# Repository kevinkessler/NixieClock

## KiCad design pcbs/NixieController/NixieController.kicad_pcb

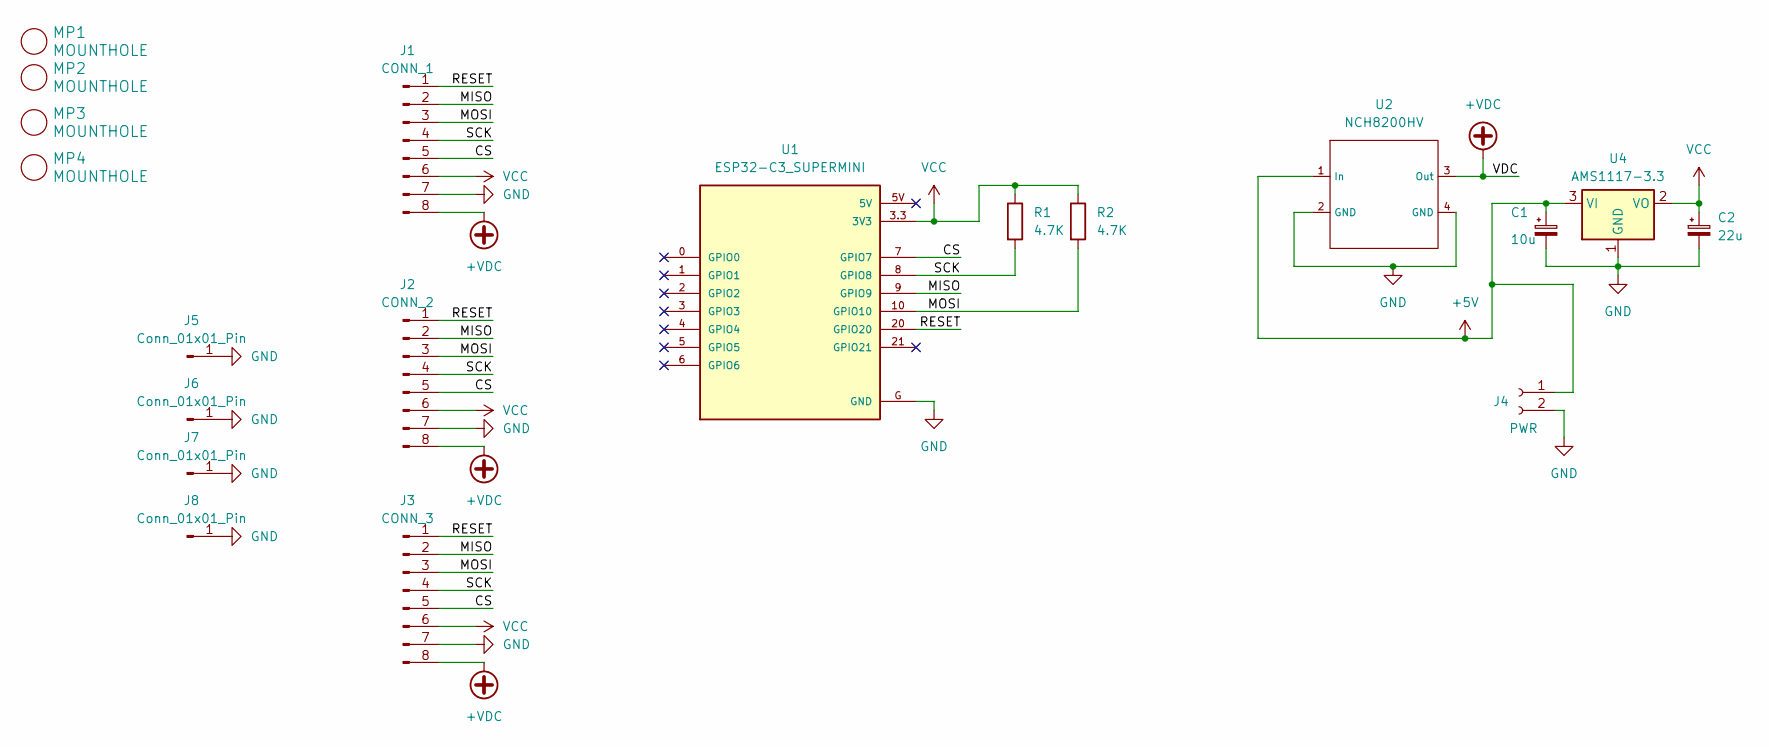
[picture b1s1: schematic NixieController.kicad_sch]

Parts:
C1: 10u; CP_Elec_5x5.3
C2: 22u; CP_Elec_6.3x7.7
J1: CONN_1; JST_PH_B8B-PH-K_1x08_P2.00mm_Vertical
J2: CONN_2; JST_PH_B8B-PH-K_1x08_P2.00mm_Vertical
J3: CONN_3; JST_PH_B8B-PH-K_1x08_P2.00mm_Vertical
J4: PWR; PinSocket_1x02_P2.54mm_Vertical
J5, J6, J7, J8: Conn_01x01_Pin; PinSocket_1x01_P2.54mm_Vertical
MP1, MP2, MP3, MP4: MOUNTHOLE; TH-M3
R1, R2: 4.7K; R_0805_2012Metric_Pad1.20x1.40mm_HandSolder
U1: ESP32-C3_SUPERMINI; MODULE_ESP32-C3_SUPERMINI
U2: NCH8200HV
U4: AMS1117-3.3; SOT-223-3_TabPin2

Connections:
+5V: C1.1, J4.1, U2.1 (In), U4.3 (VI)
+VDC: J1.8, J2.8, J3.8, U2.3 (Out)
/CS: J1.5, J2.5, J3.5, U1.7 (GPIO7)
/MISO: J1.2, J2.2, J3.2, U1.9 (GPIO9)
/MOSI: J1.3, J2.3, J3.3, R2.2, U1.10 (GPIO10)
/RESET: J1.1, J2.1, J3.1, U1.20 (GPIO20)
/SCK: J1.4, J2.4, J3.4, R1.2, U1.8 (GPIO8)
GND: C1.2, C2.2, J1.7, J2.7, J3.7, J4.2, J5.1, J6.1, J7.1, J8.1, U1.G (GND), U2.2 (GND), U2.4 (GND), U4.1 (GND)
VCC: C2.1, J1.6, J2.6, J3.6, R1.1, R2.1, U1.3.3 (3V3), U4.2 (VO)

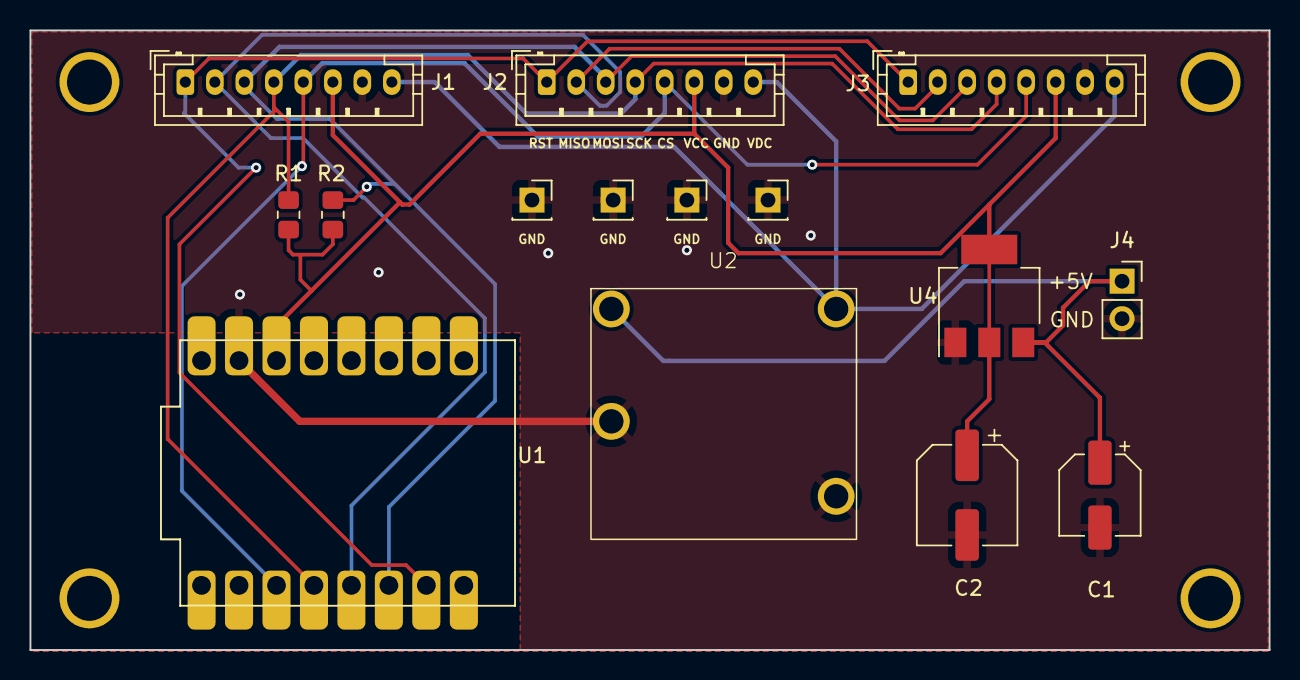
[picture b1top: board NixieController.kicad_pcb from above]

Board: 2 copper layers, 84.0 x 42.0 mm, 19 parts (0 on the bottom side), 9 nets.

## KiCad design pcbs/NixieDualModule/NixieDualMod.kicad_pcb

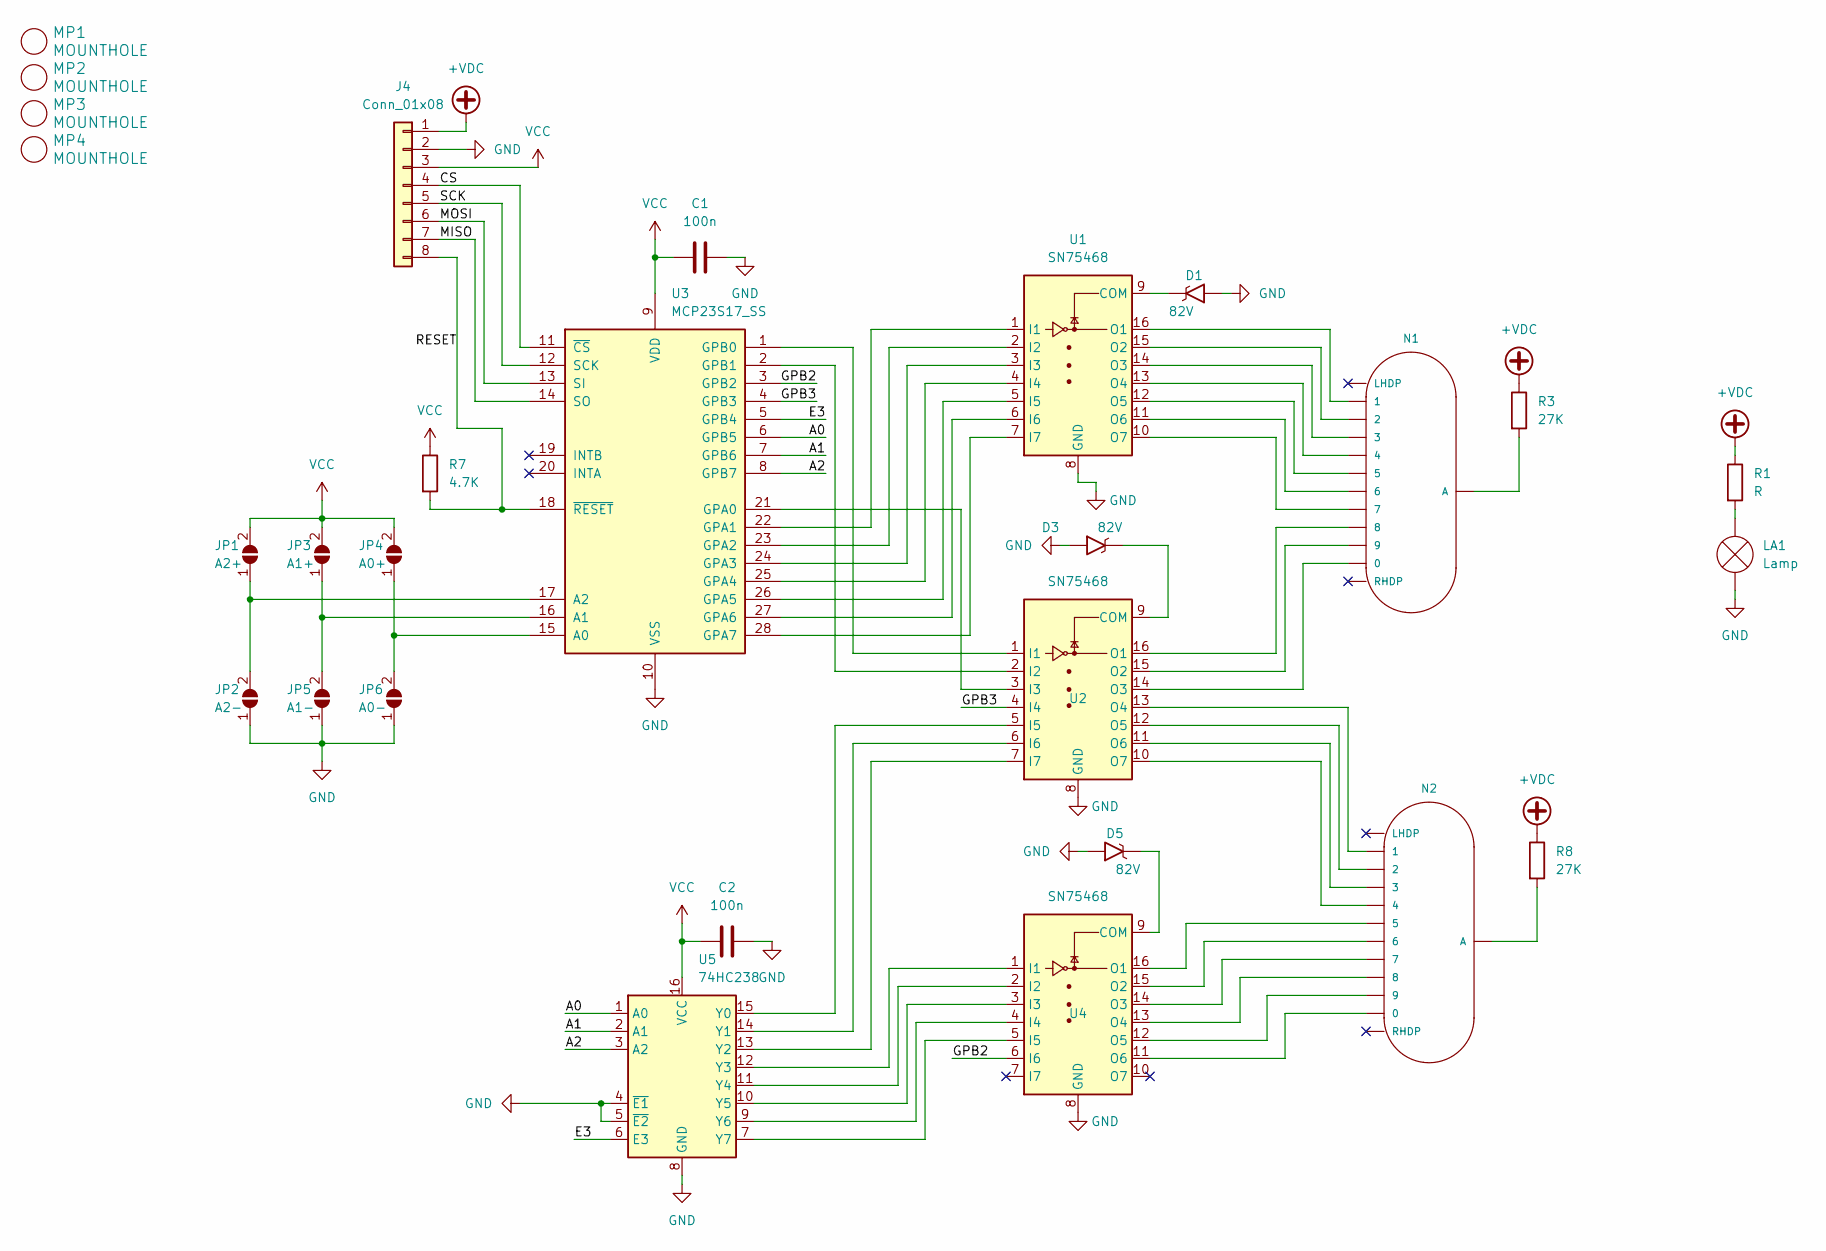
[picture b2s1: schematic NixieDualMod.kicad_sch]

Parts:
C1, C2: 100n; C_0805_2012Metric_Pad1.18x1.45mm_HandSolder
D1, D3, D5: 82V; Zener_SOT-23-3
J4: Conn_01x08; JST_PH_B8B-PH-K_1x08_P2.00mm_Vertical
JP1: A2+; SolderJumper-2_P1.3mm_Open_TrianglePad1.0x1.5mm
JP2: A2-; SolderJumper-2_P1.3mm_Open_TrianglePad1.0x1.5mm
JP3: A1+; SolderJumper-2_P1.3mm_Open_TrianglePad1.0x1.5mm
JP4: A0+; SolderJumper-2_P1.3mm_Open_TrianglePad1.0x1.5mm
JP5: A1-; SolderJumper-2_P1.3mm_Open_TrianglePad1.0x1.5mm
JP6: A0-; SolderJumper-2_P1.3mm_Open_TrianglePad1.0x1.5mm
LA1: Lamp; Valve_Glimm
MP1, MP2, MP3, MP4: MOUNTHOLE; TH-M3
N1, N2: IN-1; nixies-us-IN-14
R1: R; R_0805_2012Metric_Pad1.20x1.40mm_HandSolder
R3, R8: 27K; R_0805_2012Metric_Pad1.20x1.40mm_HandSolder
R7: 4.7K; R_0805_2012Metric_Pad1.20x1.40mm_HandSolder
U1, U2, U4: SN75468; SOIC-16_3.9x9.9mm_P1.27mm
U3: MCP23S17_SS; SOIC-28W_7.5x17.9mm_P1.27mm
U5: 74HC238; SOP-16_3.9x9.9mm_P1.27mm

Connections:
+VDC: J4.1, R1.1, R3.1, R8.1
/A0: U3.6 (GPB5), U5.1 (A0)
/A1: U3.7 (GPB6), U5.2 (A1)
/A2: U3.8 (GPB7), U5.3 (A2)
/CS: J4.4, U3.11 (~CS)
/E3: U3.5 (GPB4), U5.6 (E3)
/GPB2: U3.3 (GPB2), U4.6 (I6)
/GPB3: U2.4 (I4), U3.4 (GPB3)
/MISO: J4.7, U3.14 (SO)
/MOSI: J4.6, U3.13 (SI)
/RESET: J4.8, R7.2, U3.18 (~RESET)
/SCK: J4.5, U3.12 (SCK)
GND: C1.2, C2.2, D1.1 (A), D3.1 (A), D5.1 (A), J4.2, JP2.1 (A), JP5.1 (A), JP6.1 (A), LA1.1 (-), U1.8 (GND), U2.8 (GND), U3.10 (VSS), U4.8 (GND), U5.4 (~E1), U5.5 (~E2), U5.8 (GND)
unnamed: D1.3 (K), U1.9 (COM)
unnamed: D3.3 (K), U2.9 (COM)
unnamed: D5.3 (K), U4.9 (COM)
unnamed: JP1.1 (A), JP2.2 (B), U3.17 (A2)
unnamed: JP3.1 (A), JP5.2 (B), U3.16 (A1)
unnamed: JP4.1 (A), JP6.2 (B), U3.15 (A0)
unnamed: LA1.2 (+), R1.2
unnamed: N1.A, R3.2
unnamed: N2.A, R8.2
unnamed: U1.1 (I1), U3.22 (GPA1)
unnamed: U1.2 (I2), U3.23 (GPA2)
unnamed: U1.3 (I3), U3.24 (GPA3)
unnamed: U1.4 (I4), U3.25 (GPA4)
unnamed: U1.5 (I5), U3.26 (GPA5)
unnamed: U1.6 (I6), U3.27 (GPA6)
unnamed: U1.7 (I7), U3.28 (GPA7)
unnamed: N1.1, U1.16 (O1)
unnamed: N1.2, U1.15 (O2)
unnamed: N1.3, U1.14 (O3)
unnamed: N1.4, U1.13 (O4)
unnamed: N1.5, U1.12 (O5)
unnamed: N1.6, U1.11 (O6)
unnamed: N1.7, U1.10 (O7)
unnamed: U2.1 (I1), U3.1 (GPB0)
unnamed: U2.2 (I2), U3.2 (GPB1)
unnamed: U2.3 (I3), U3.21 (GPA0)
unnamed: U2.5 (I5), U5.15 (Y0)
unnamed: U2.6 (I6), U5.14 (Y1)
unnamed: U2.7 (I7), U5.13 (Y2)
unnamed: N1.8, U2.16 (O1)
unnamed: N1.9, U2.15 (O2)
unnamed: N1.0, U2.14 (O3)
unnamed: N2.1, U2.13 (O4)
unnamed: N2.2, U2.12 (O5)
unnamed: N2.3, U2.11 (O6)
unnamed: N2.4, U2.10 (O7)
unnamed: U4.1 (I1), U5.12 (Y3)
unnamed: U4.2 (I2), U5.11 (Y4)
unnamed: U4.3 (I3), U5.10 (Y5)
unnamed: U4.4 (I4), U5.9 (Y6)
unnamed: U4.5 (I5), U5.7 (Y7)
unnamed: N2.5, U4.16 (O1)
unnamed: N2.6, U4.15 (O2)
unnamed: N2.7, U4.14 (O3)
unnamed: N2.8, U4.13 (O4)
unnamed: N2.9, U4.12 (O5)
unnamed: N2.0, U4.11 (O6)
VCC: C1.1, C2.1, J4.3, JP1.2 (B), JP3.2 (B), JP4.2 (B), R7.1, U3.9 (VDD), U5.16 (VCC)

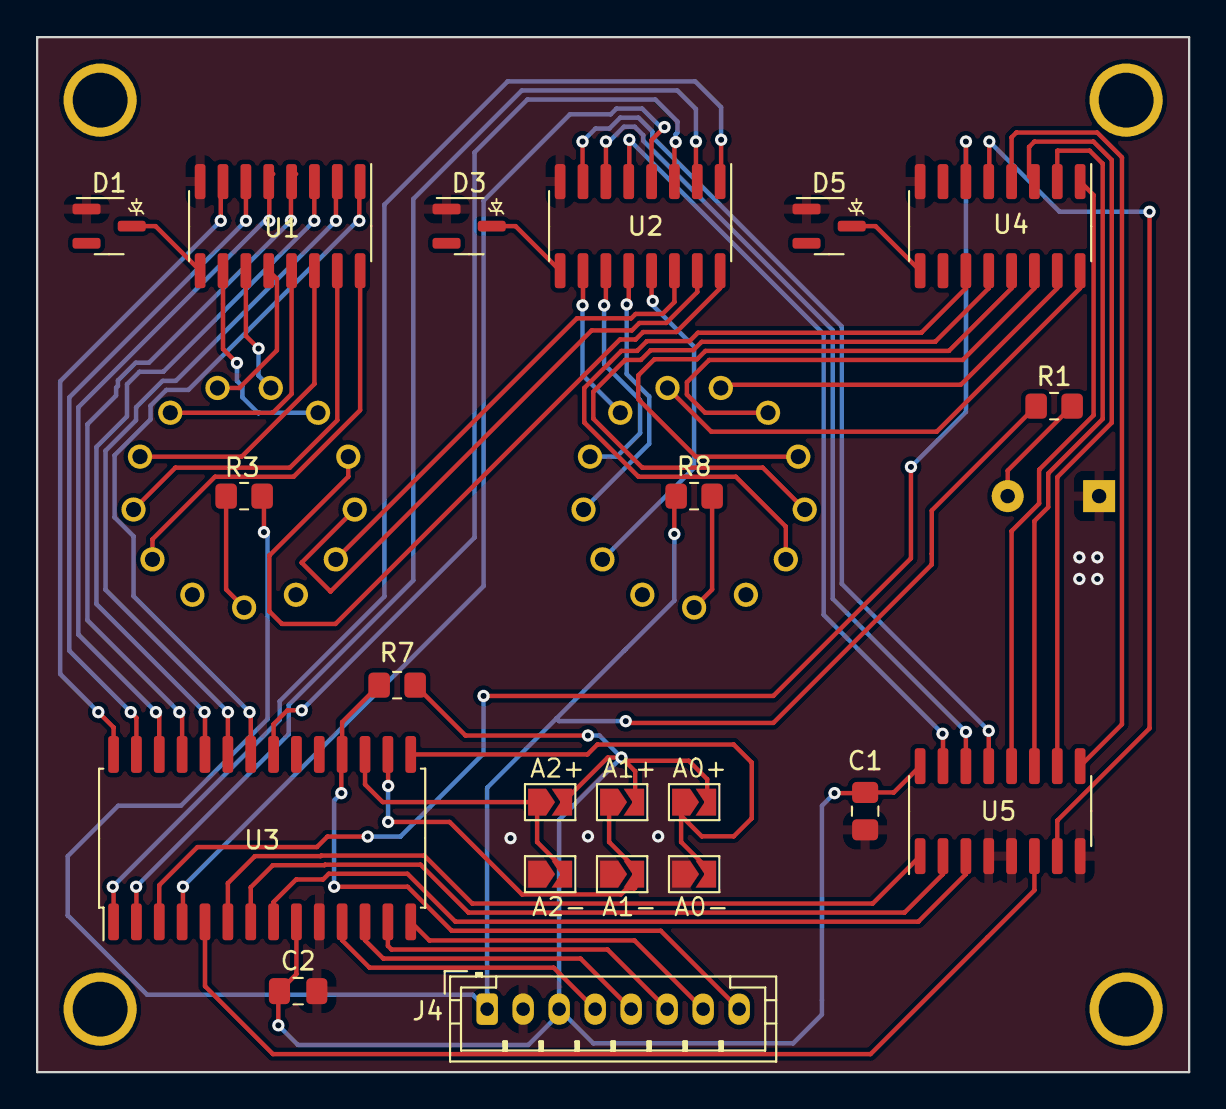
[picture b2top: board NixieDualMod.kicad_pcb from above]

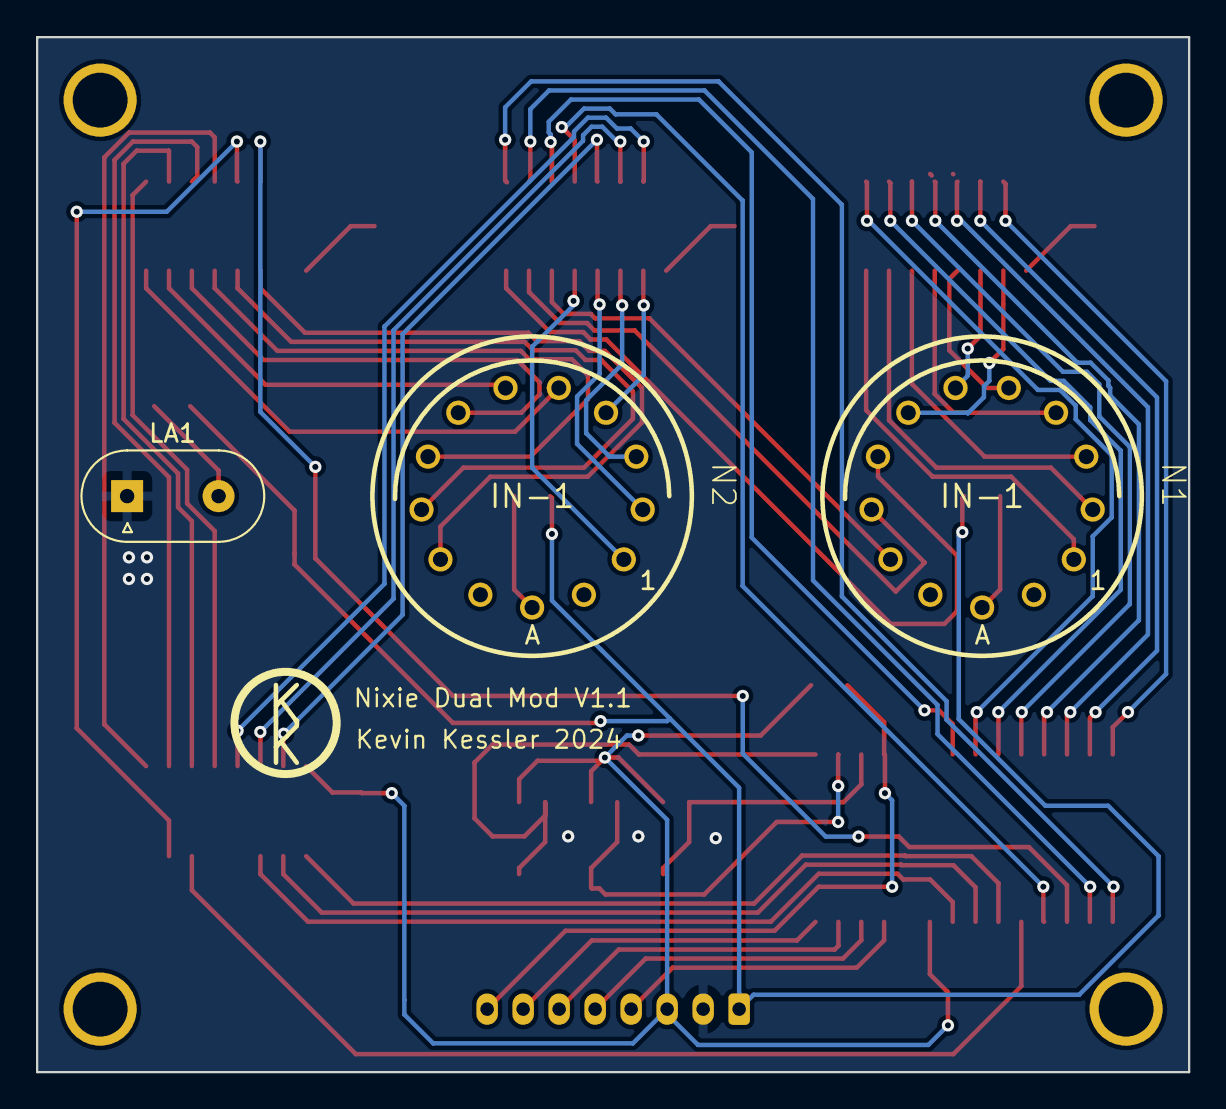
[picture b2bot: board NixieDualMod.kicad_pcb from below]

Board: 2 copper layers, 64.0 x 57.5 mm, 28 parts (3 on the bottom side), 61 nets.

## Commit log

2024-05-15 Working Clock
2024-05-20 12th Hour
